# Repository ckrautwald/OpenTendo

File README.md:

<br />

# Open 'Tendo

This fork develops modern component substitutions. The motherboard now replaces
RA2 with four 0805 resistors (R20–R23). See [RA2 modernization](RA2-MODERNIZATION.md)
for the change, validation results, and prototype limitations. Open the board in
KiCad 10.
An Open-Source HardWare (OSHW) recreation of the original 1985 Front-Loading NES motherboard.

## Note on RGB and HDMI

Neither RGB nor HDMI video output were or are a goal of the OpenTendo project, the goal was/is documentation and preservation, and the project was an exercise in reverse engineering. As such "improved" video outputs will not be added to OpenTendo.

NESRGB and Hi-Def NES can be installed as normal, but will not be incorporated into the OpenTendo PCB

## Repository Structure
### Branches
| Branch | Description |
| ------ | ----------- |
| master | Latest revision of OpenTendo. This is a almost 1:1 of the OEM NES. |
| modded | Modded version of the latest revision (`master`). This houses any modification that is not in the OEM NES. |
| vX.X | Previous revisions of OpenTendo. (*ex.* v1.3) |
| vX.X_modded | Modded version of a previous revision. (*ex.* v1.3_modded) |

### File Structure
```
.
├── BOM              # Contains the bill of materials.
├── Board Files      # Contains all files necessary to open the project in KiCad.
|   └── Libraries    # Contains a library of all of the custom footprints used on the board.
├── Scans            # Contains the scans of the OEM NES board.
└── Schematics       # Contains schematics for the OEM frontloading NES board revisions,
                       some schematics represent more than one revision
```

The gerber files required to order PCBs can be found under [releases](https://github.com/Redherring32/OpenTendo/releases).

## Recommended PCB specs
* 2 layers

* 119mmx196mm

* 1.6mm thickness

* HASL or ENiG surface finish

* And any color you want!

> [!IMPORTANT]
> OpenTendo have some solder mask overlapping the edge connector to secure the pads and the thin traces. Some fabricators might see this as an error and might try to fix it.
>
> We recommend leaving a note saying that the solder mask overlap on the edge connector is intentional and NOT an error when ordering the PCB.

The design is as true to the original board as possible, with subtle changes where needed to compensate for outdated/unsourcable parts,
as well as some improvements. (Expansion audio enabled, and other minor changes)

Since this project is open-source you may do as you like with it, whether that is to make boards for personal use, sell replacement NES boards, or to use the provided info for further custom PCB work/designs.

I am not in any way affiliated with Nintendo, I'm just doing this in my free time as a stepping stone into further Reverse Engineering work.

>[!NOTE]
> Please check the [BOM](./BOM#from-the-oem-nes) for the list of components needed from the OEM NES

## License

Licensed under
the TAPR Open Hardware License (www.tapr.org/OHL)

©Redherring32 2019-2024

## Credits
*=Lockster=* - Helping me tremendously along the way, keeping me from going insane, and cleaning up/helping with the final schematic. 

*Krzysiobal* - Putting together the NES-CPU-11 schematic that my schematic is largely referrenced against.

*[Muramasa](https://www.muramasaentertainment.com/)* - Ported to KiCad v8, PCB clean up, and fixing the EXP port footprint.

*[Kamoteshake](https://github.com/kamoteshake)* - Schematic clean up and fixing the EXP port footprint.

And to all of the awesome people in the NES scene, I wouldn't have been able to do this without the awesome work that some very clever people did before I got here.

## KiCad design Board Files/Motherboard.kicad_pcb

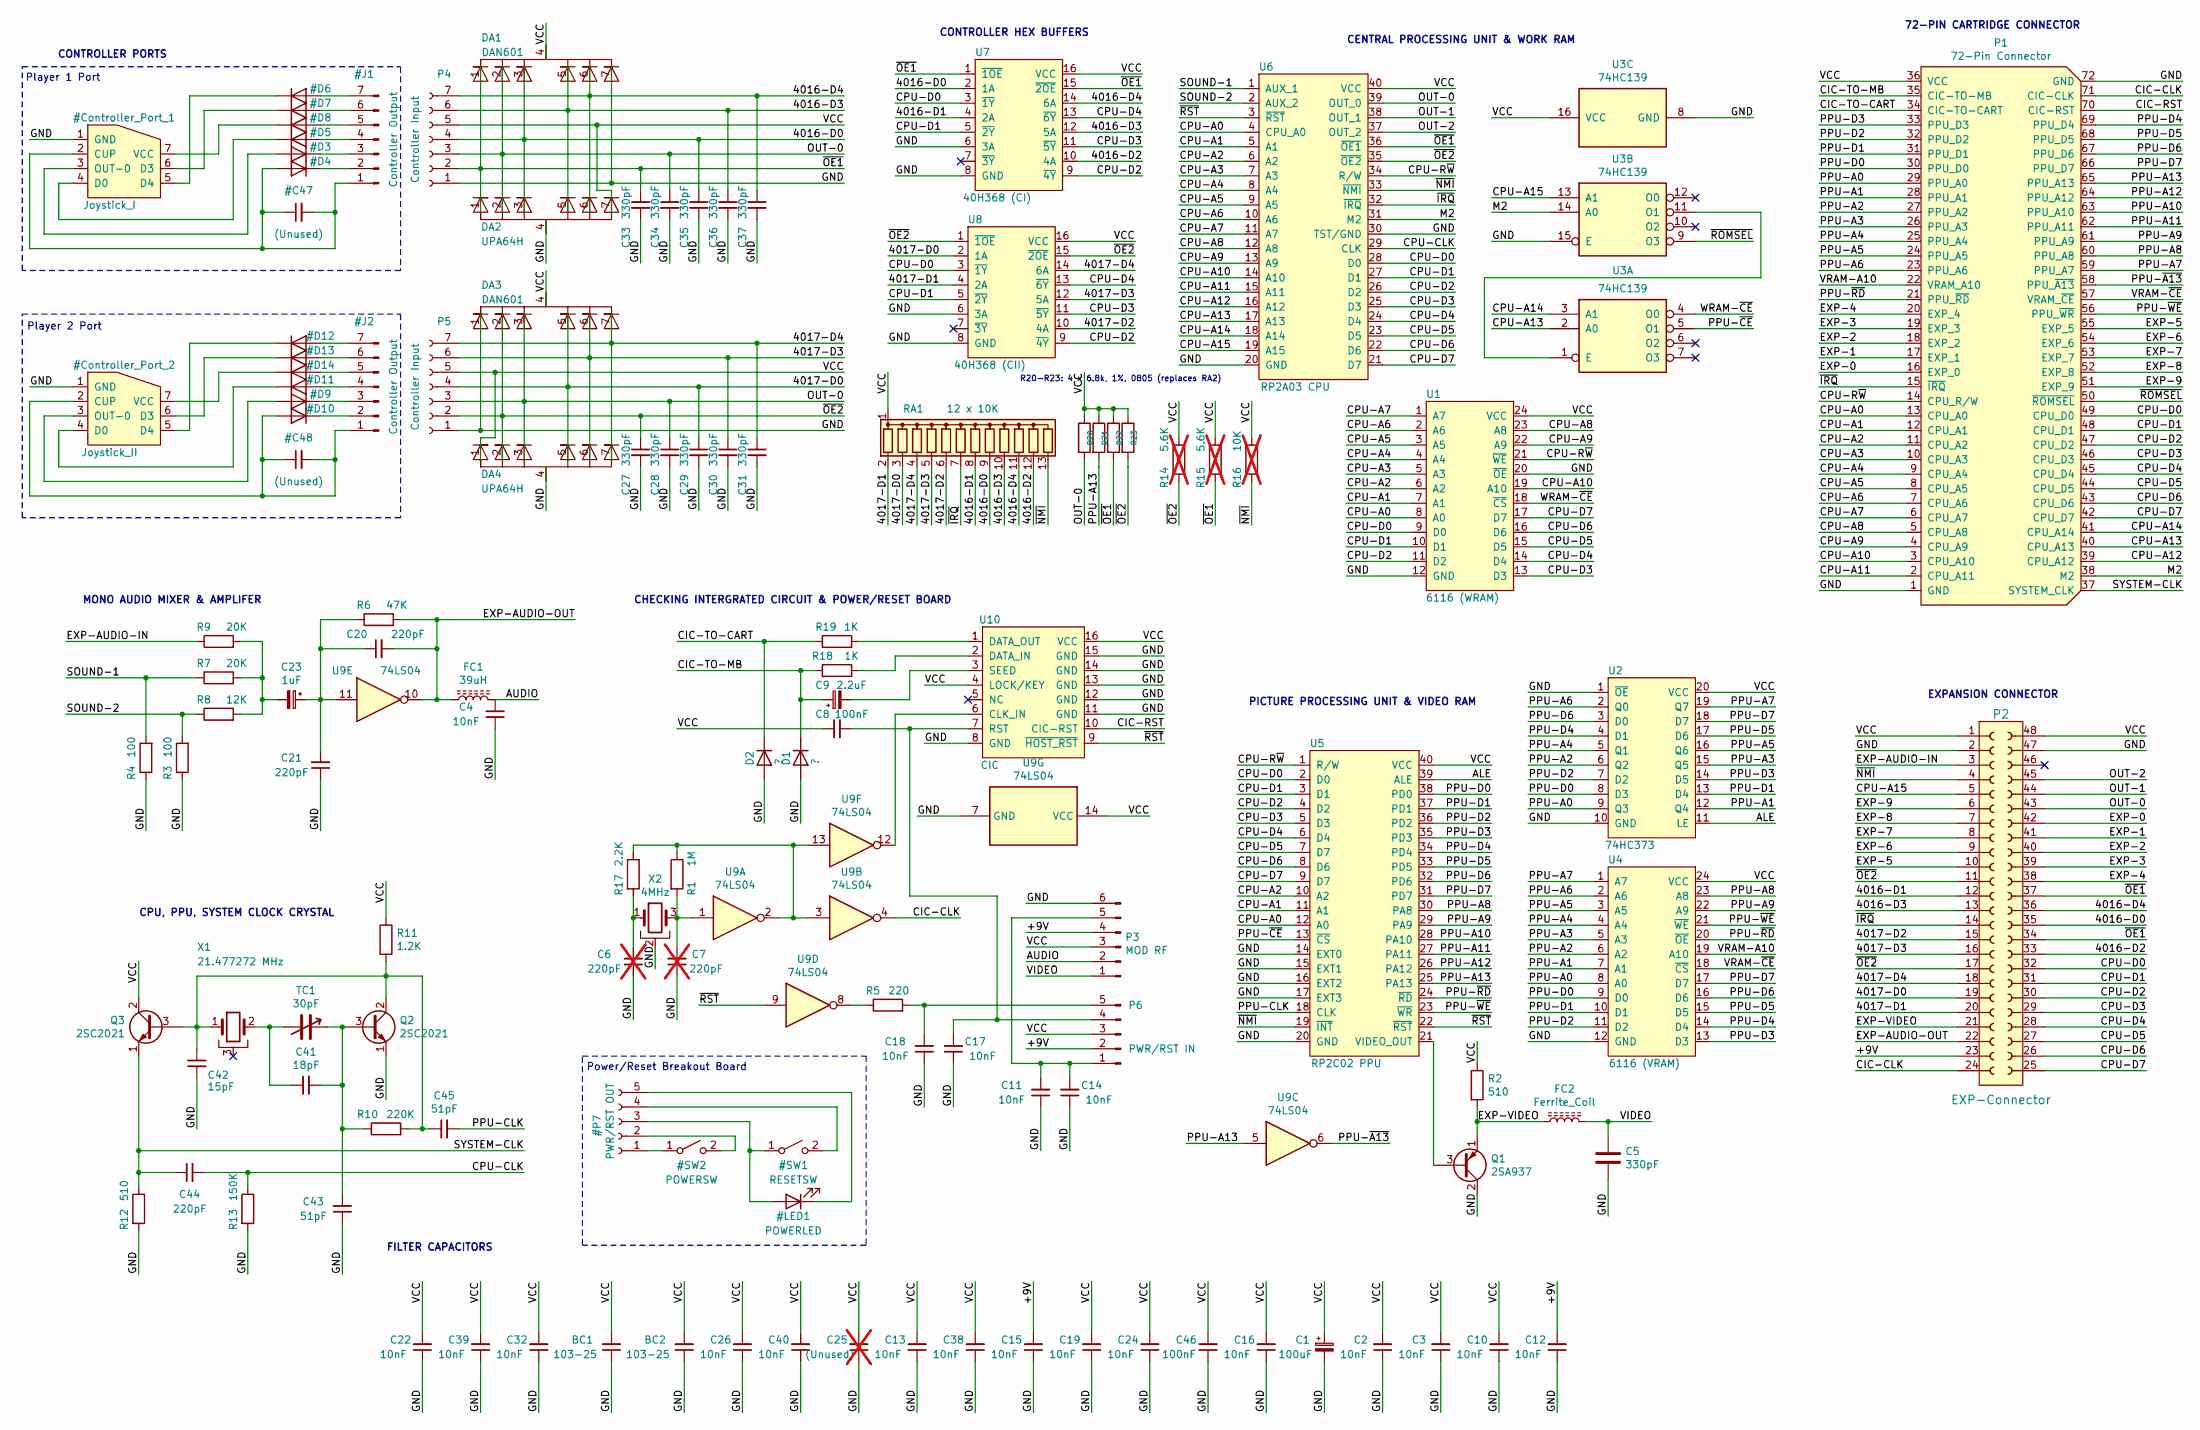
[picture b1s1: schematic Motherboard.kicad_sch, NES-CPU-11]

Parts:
BC1, BC2: 103-25; C_Disc_D6.0mm_W2.5mm_P5.00mm
C1: 100uF; CP_Radial_D5.0mm_P2.50mm
C2, C3, C4, C10, C11, C12, C13, C14, C15, C16, C17, C18, C19, C22, C24, C26, C32, C38, C39, C40: 10nF; C_Disc_D5.0mm_W2.5mm_P5.00mm
C5: 330pF; C_Disc_D3.0mm_W2.0mm_P2.50mm
C6, C7: 220pF; C_Disc_D3.0mm_W1.6mm_P2.50mm; not fitted
C8, C46: 100nF; C_Disc_D7.0mm_W2.5mm_P5.00mm
C9: 2.2uF; CP_Radial_D5.0mm_P2.50mm
C20, C21, C44: 220pF; C_Disc_D3.0mm_W1.6mm_P2.50mm
C23: 1uF; CP_Radial_D5.0mm_P2.50mm
C25: (Unused); C_Disc_D5.0mm_W2.5mm_P5.00mm; not fitted
C27, C28, C29, C30, C31, C33, C34, C35, C36, C37: 330pF; C_Disc_D3.0mm_W1.6mm_P2.50mm
C41: 18pF; C_Disc_D3.0mm_W2.0mm_P2.50mm
C42: 15pF; C_Disc_D3.4mm_W2.1mm_P2.50mm
C43, C45: 51pF; C_Disc_D3.4mm_W2.1mm_P2.50mm
D1, D2: ?; D_DO-35_SOD27_P10.16mm_Horizontal
DA1, DA3: DAN601; R_Array_SIP7
DA2, DA4: UPA64H; R_Array_SIP7
FC1: 39uH; R_Axial_DIN0207_L6.3mm_D2.5mm_P10.16mm_Horizontal
FC2: Ferrite_Coil; R_Axial_DIN0207_L6.3mm_D2.5mm_P10.16mm_Horizontal
P1: 72-Pin Connector; NES_Edge_Connector
P2: EXP-Connector; EXP_Header
P3: MOD RF; Mod_RF
P4, P5: Controller Input; JST_PH_S7B-PH-K_1x07_P2.00mm_Horizontal
P6: PWR/RST IN; PowerReset-switch-In
Q1: 2SA937; TO-126-3_Vertical_Short
Q2, Q3: 2SC2021; TO-126-3_Vertical_Short
R1: 1M; R_Axial_DIN0207_L6.3mm_D2.5mm_P10.16mm_Horizontal
R2, R12: 510; R_Axial_DIN0207_L6.3mm_D2.5mm_P10.16mm_Horizontal
R3, R4: 100; R_Axial_DIN0207_L6.3mm_D2.5mm_P10.16mm_Horizontal
R5: 220; R_Axial_DIN0207_L6.3mm_D2.5mm_P10.16mm_Horizontal
R6: 47K; R_Axial_DIN0207_L6.3mm_D2.5mm_P10.16mm_Horizontal
R7, R9: 20K; R_Axial_DIN0207_L6.3mm_D2.5mm_P10.16mm_Horizontal
R8: 12K; R_Axial_DIN0207_L6.3mm_D2.5mm_P10.16mm_Horizontal
R10: 220K; R_Axial_DIN0207_L6.3mm_D2.5mm_P10.16mm_Horizontal
R11: 1.2K; R_Axial_DIN0207_L6.3mm_D2.5mm_P10.16mm_Horizontal
R13: 150K; R_Axial_DIN0207_L6.3mm_D2.5mm_P10.16mm_Horizontal
R14, R15: 5.6K; R_Axial_DIN0207_L6.3mm_D2.5mm_P10.16mm_Horizontal; not fitted
R16: 10K; R_Axial_DIN0207_L6.3mm_D2.5mm_P10.16mm_Horizontal; not fitted
R17: 2.2K; R_Axial_DIN0207_L6.3mm_D2.5mm_P10.16mm_Horizontal
R18, R19: 1K; R_Axial_DIN0207_L6.3mm_D2.5mm_P10.16mm_Horizontal
R20, R21, R22, R23: 6.8k; R_0805_2012Metric_Pad1.20x1.40mm_HandSolder; MPN RC0805FR-076K8L
RA1: 12 x 10K; R_Array_SIP13
TC1: 30pF; TrimmerCap-THT
U1: 6116 (WRAM); DIP-24_W15.24-7.62mm
U2: 74HC373; DIP-20_W7.62mm
U3: 74HC139; DIP-16_W7.62mm
U4: 6116 (VRAM); DIP-24_W15.24-7.62mm
U5: RP2C02 PPU; DIP-40_W15.24mm
U6: RP2A03 CPU; DIP-40_W15.24mm
U7: 40H368 (CI); DIP-16_W7.62mm
U8: 40H368 (CII); DIP-16_W7.62mm
U9: 74LS04; DIP-14_W7.62mm
U10: CIC; DIP-16_W7.62mm
X1: 21.477272 MHz; Crystal_HC49-U_Horizontal_1EP_style2
X2: 4MHz; Resonator_Murata_CSTLSxxxG-3Pin_W8.0mm_H3.0mm

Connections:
/4016-D0: C35.1, DA1.3, DA2.3, P2.35, P4.4, RA1.9 (R8), U7.2 (1A)
/4016-D1: P2.12, RA1.8 (R7), U7.4 (2A)
/4016-D2: P2.33, RA1.12 (R11), U7.10 (4A)
/4016-D3: C36.1, DA1.5, DA2.5, P2.13, P4.6, RA1.10 (R9), U7.12 (5A)
/4016-D4: C37.1, DA1.6, DA2.6, P2.36, P4.7, RA1.11 (R10), U7.14 (6A)
/4017-D0: C29.1, DA3.5, DA4.5, P2.19, P5.4, RA1.3 (R2), U8.2 (1A)
/4017-D1: P2.20, RA1.2 (R1), U8.4 (2A)
/4017-D2: P2.15, RA1.6 (R5), U8.10 (4A)
/4017-D3: C30.1, DA3.6, DA4.6, P2.16, P5.6, RA1.5 (R4), U8.12 (5A)
/4017-D4: C31.1, DA3.7, DA4.7, P2.18, P5.7, RA1.4 (R3), U8.14 (6A)
/+9V: C12.2, C15.2, P2.23, P3.4, P6.2
/ALE: U2.11 (LE), U5.39 (ALE)
/AUDIO: C4.2, FC1.2, P3.2
/CIC-CLK: P1.71 (CIC-CLK), P2.24, U9.4
/CIC-RST: P1.70 (CIC-RST), U10.10 (CIC-RST)
/CIC-TO-CART: D2.1 (K), P1.34 (CIC-TO-CART), R19.1
/CIC-TO-MB: C9.1, D1.1 (K), P1.35 (CIC-TO-MB), R18.1
/CPU-A0: P1.13 (CPU_A0), U1.8 (A0), U5.12 (A0), U6.4 (CPU_A0)
/CPU-A1: P1.12 (CPU_A1), U1.7 (A1), U5.11 (A1), U6.5 (A1)
/CPU-A2: P1.11 (CPU_A2), U1.6 (A2), U5.10 (A2), U6.6 (A2)
/CPU-A3: P1.10 (CPU_A3), U1.5 (A3~), U6.7 (A3)
/CPU-A4: P1.9 (CPU_A4), U1.4 (A4~), U6.8 (A4)
/CPU-A5: P1.8 (CPU_A5), U1.3 (A5~), U6.9 (A5)
/CPU-A6: P1.7 (CPU_A6), U1.2 (A6~), U6.10 (A6)
/CPU-A7: P1.6 (CPU_A7), U1.1 (A7), U6.11 (A7)
/CPU-A8: P1.5 (CPU_A8), U1.23 (A8), U6.12 (A8)
/CPU-A9: P1.4 (CPU_A9), U1.22 (A9), U6.13 (A9)
/CPU-A10: P1.3 (CPU_A10), U1.19 (A10), U6.14 (A10)
/CPU-A11: P1.2 (CPU_A11), U6.15 (A11)
/CPU-A12: P1.39 (CPU_A12), U6.16 (A12)
/CPU-A13: P1.40 (CPU_A13), U3.2 (A0), U6.17 (A13)
/CPU-A14: P1.41 (CPU_A14), U3.3 (A1), U6.18 (A14)
/CPU-A15: P2.5, U3.13 (A1), U6.19 (A15)
/CPU-CLK: C44.2, R13.1, U6.29 (CLK)
/CPU-D0: P1.49 (CPU_D0), P2.32, U1.9 (D0), U5.2 (D0), U6.28 (D0), U7.3 (~1Y), U8.3 (~1Y)
/CPU-D1: P1.48 (CPU_D1), P2.31, U1.10 (D1), U5.3 (D1), U6.27 (D1), U7.5 (~2Y), U8.5 (~2Y)
/CPU-D2: P1.47 (CPU_D2), P2.30, U1.11 (D2), U5.4 (D2), U6.26 (D2), U7.9 (~4Y), U8.9 (~4Y)
/CPU-D3: P1.46 (CPU_D3), P2.29, U1.13 (D3), U5.5 (D3), U6.25 (D3), U7.11 (~5Y), U8.11 (~5Y)
/CPU-D4: P1.45 (CPU_D4), P2.28, U1.14 (D4), U5.6 (D4), U6.24 (D4), U7.13 (~6Y), U8.13 (~6Y)
/CPU-D5: P1.44 (CPU_D5), P2.27, U1.15 (D5), U5.7 (D7), U6.23 (D5)
/CPU-D6: P1.43 (CPU_D6), P2.26, U1.16 (D6), U5.8 (D6), U6.22 (D6)
/CPU-D7: P1.42 (CPU_D7), P2.25, U1.17 (D7), U5.9 (D7), U6.21 (D7)
/CPU-R~W: P1.14 (CPU_R/W), U1.21 (~WE), U5.1 (R/W), U6.34 (R/W)
/EXP-0: P1.16 (EXP_0), P2.42
/EXP-1: P1.17 (EXP_1), P2.41
/EXP-2: P1.18 (EXP_2), P2.40
/EXP-3: P1.19 (EXP_3), P2.39
/EXP-4: P1.20 (EXP_4), P2.38
/EXP-5: P1.55 (EXP_5), P2.10
/EXP-6: P1.54 (EXP_6), P2.9
/EXP-7: P1.53 (EXP_7), P2.8
/EXP-8: P1.52 (EXP_8), P2.7
/EXP-9: P1.51 (EXP_9), P2.6
/EXP-AUDIO-IN: P2.3, R9.1
/EXP-AUDIO-OUT: C20.2, FC1.1, P2.22, R6.2, U9.10
/EXP-VIDEO: FC2.1, P2.21, Q1.1 (E), R2.2
/GND: BC1.1, BC2.1, C1.2, C2.1, C3.1, C4.1, C5.2, C6.1, C7.1, C10.1, C11.1, C12.1, C13.1, C14.1, C15.1, C16.1, C17.1, C18.1, C19.1, C21.1, C22.1, C24.1, C25.1, C26.1, C27.2, C28.2, C29.2, C30.2, C31.2, C32.1, C33.2, C34.2, C35.2, C36.2, C37.2, C38.1, C39.1, C40.1, C42.1, C43.1, C46.1, D1.2 (A), D2.2 (A), DA1.7, DA2.4, DA3.1, DA4.4, P1.1 (GND), P1.72 (GND), P2.2, P2.47, P3.6, P4.1, P5.1, Q1.2 (C), Q2.1 (E), R3.1, R4.1, R12.2, R13.2, U1.12 (GND~), U1.20 (~OE), U2.1 (~OE), U2.10 (GND), U3.8 (GND), U3.15 (E), U4.12 (GND~), U5.14 (EXT0), U5.15 (EXT1), U5.16 (EXT2), U5.17 (EXT3), U5.20 (GND), U6.20 (GND), U6.30 (TST/GND), U7.6 (3A), U7.8 (GND), U8.6 (3A), U8.8 (GND), U9.7 (GND), U10.8 (GND), U10.11 (GND), U10.12 (GND), U10.13 (GND), U10.14 (GND), U10.15 (GND), X2.2
/M2: P1.38 (M2), U3.14 (A0), U6.31 (M2)
/OUT-0: C28.1, C34.1, DA1.2, DA2.2, DA3.3, DA4.3, P2.43, P4.3, P5.3, R20.2, U6.39 (OUT_0)
/OUT-1: P2.44, U6.38 (OUT_1)
/OUT-2: P2.45, U6.37 (OUT_2)
/PPU-A0: P1.29 (PPU_A0), U2.9 (Q3), U4.8 (A0)
/PPU-A1: P1.28 (PPU_A1), U2.12 (Q4), U4.7 (A1)
/PPU-A2: P1.27 (PPU_A2), U2.6 (Q2), U4.6 (A2)
/PPU-A3: P1.26 (PPU_A3), U2.15 (Q5), U4.5 (A3~)
/PPU-A4: P1.25 (PPU_A4), U2.5 (Q1), U4.4 (A4~)
/PPU-A5: P1.24 (PPU_A5), U2.16 (Q6), U4.3 (A5~)
/PPU-A6: P1.23 (PPU_A6), U2.2 (Q0), U4.2 (A6~)
/PPU-A7: P1.59 (PPU_A7), U2.19 (Q7), U4.1 (A7)
/PPU-A8: P1.60 (PPU_A8), U4.23 (A8), U5.30 (PA8)
/PPU-A9: P1.61 (PPU_A9), U4.22 (A9), U5.29 (PA9)
/PPU-A10: P1.63 (PPU_A10), U5.28 (PA10)
/PPU-A11: P1.62 (PPU_A11), U5.27 (PA11)
/PPU-A12: P1.64 (PPU_A12), U5.26 (PA12)
/PPU-A13: P1.65 (PPU_A13), R21.2, U5.25 (PA13), U9.5
/PPU-CLK: C45.2, U5.18 (CLK)
/PPU-D0: P1.30 (PPU_D0), U2.8 (D3), U4.9 (D0), U5.38 (PD0)
/PPU-D1: P1.31 (PPU_D1), U2.13 (D4), U4.10 (D1), U5.37 (PD1)
/PPU-D2: P1.32 (PPU_D2), U2.7 (D2), U4.11 (D2), U5.36 (PD2)
/PPU-D3: P1.33 (PPU_D3), U2.14 (D5), U4.13 (D3), U5.35 (PD3)
/PPU-D4: P1.69 (PPU_D4), U2.4 (D1), U4.14 (D4), U5.34 (PD4)
/PPU-D5: P1.68 (PPU_D5), U2.17 (D6), U4.15 (D5), U5.33 (PD5)
/PPU-D6: P1.67 (PPU_D6), U2.3 (D0), U4.16 (D6), U5.32 (PD6)
/PPU-D7: P1.66 (PPU_D7), U2.18 (D7), U4.17 (D7), U5.31 (PD7)
/PPU-~A13: P1.58 (PPU_~A13), U9.6
/PPU-~CE: U3.5 (O1), U5.13 (~CS)
/PPU-~RD: P1.21 (PPU_~RD), U4.20 (~OE), U5.24 (~RD)
/PPU-~WE: P1.56 (PPU_~WR), U4.21 (~WE), U5.23 (~WR)
/SOUND-1: R4.2, R7.1, U6.1 (AUX_1)
/SOUND-2: R3.2, R8.1, U6.2 (AUX_2)
/SYSTEM-CLK: C44.1, P1.37 (SYSTEM_CLK), Q3.1 (E), R12.1
/VCC: BC1.2, BC2.2, C1.1, C2.2, C3.2, C8.1, C10.2, C13.2, C16.2, C19.2, C22.2, C24.2, C25.2, C26.2, C32.2, C38.2, C39.2, C40.2, C46.2, DA1.4, DA2.7, DA3.4, DA4.1, P1.36 (VCC), P2.1, P2.48, P3.3, P4.5, P5.5, P6.3, Q3.2 (C), R2.1, R11.1, R14.1, R15.1, R16.1, R20.1, R21.1, R22.1, R23.1, RA1.1 (common), U1.24 (VCC), U2.20 (VCC), U3.16 (VCC), U4.24 (VCC), U5.40 (VCC), U6.40 (VCC), U7.16 (VCC), U8.16 (VCC), U9.14 (VCC), U10.4 (LOCK/KEY), U10.16 (VCC)
/VIDEO: C5.1, FC2.2, P3.1
/VRAM-A10: P1.22 (VRAM_A10), U4.19 (A10)
/VRAM-~CE: P1.57 (VRAM_~CE), U4.18 (~CS)
/WRAM-~CE: U1.18 (~CS), U3.4 (O0)
/~IRQ: P1.15 (~IRQ), P2.14, RA1.7 (R6), U6.32 (~IRQ)
/~NMI: P2.4, R16.2, RA1.13 (R12), U5.19 (~INT), U6.33 (~NMI)
/~OE1: C33.1, DA1.1, DA2.1, P2.34, P2.37, P4.2, R15.2, R22.2, U6.36 (~OE1), U7.1 (~1OE), U7.15 (~2OE)
/~OE2: C27.1, DA3.2, DA4.2, P2.11, P2.17, P5.2, R14.2, R23.2, U6.35 (~OE2), U8.1 (~1OE), U8.15 (~2OE)
/~ROMSEL: P1.50 (~ROMSEL), U3.9 (O3)
/~RST: U5.22 (~RST), U6.3 (~RST), U9.9, U10.9 (~HOST_RST)
unnamed: C6.2, R17.2, X2.1
unnamed: C7.2, R1.2, U9.1, X2.3
unnamed: C20.1, C21.2, C23.1, R6.1, U9.11
unnamed: C23.2, R7.2, R8.2, R9.2
unnamed: C41.1, TC1.2, X1.2
unnamed: C11.2, C14.2, P3.5, P6.1
unnamed: C8.2, C17.2, P6.4, U10.7 (RST)
unnamed: C18.2, P6.5, R5.2
unnamed: Q1.3 (B), U5.21 (VIDEO_OUT)
unnamed: C41.2, C43.2, Q2.3 (B), R10.1, TC1.1
unnamed: C42.2, C45.1, Q2.2 (C), Q3.3 (B), R10.2, R11.2, X1.1
unnamed: R1.1, R17.1, U9.2, U9.3, U9.13
unnamed: R5.1, U9.8
unnamed: U3.1 (E), U3.11 (O1)
unnamed: U9.12, U10.6 (CLK_IN)
unnamed: R18.2, U10.2 (DATA_IN)
unnamed: R19.2, U10.1 (DATA_OUT)
unnamed: C9.2, U10.3 (SEED)

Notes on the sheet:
72-PIN CARTRIDGE CONNECTOR
MONO AUDIO MIXER & AMPLIFER
CENTRAL PROCESSING UNIT & WORK RAM
CONTROLLER PORTS
EXPANSION CONNECTOR
FILTER CAPACITORS
Player 2 Port
Player 1 Port
Power/Reset Breakout Board
CHECKING INTERGRATED CIRCUIT & POWER/RESET BOARD
PICTURE PROCESSING UNIT & VIDEO RAM
CPU, PPU, SYSTEM CLOCK CRYSTAL
CONTROLLER HEX BUFFERS
R20-R23: 4 x 6.8k, 1%, 0805 (replaces RA2)

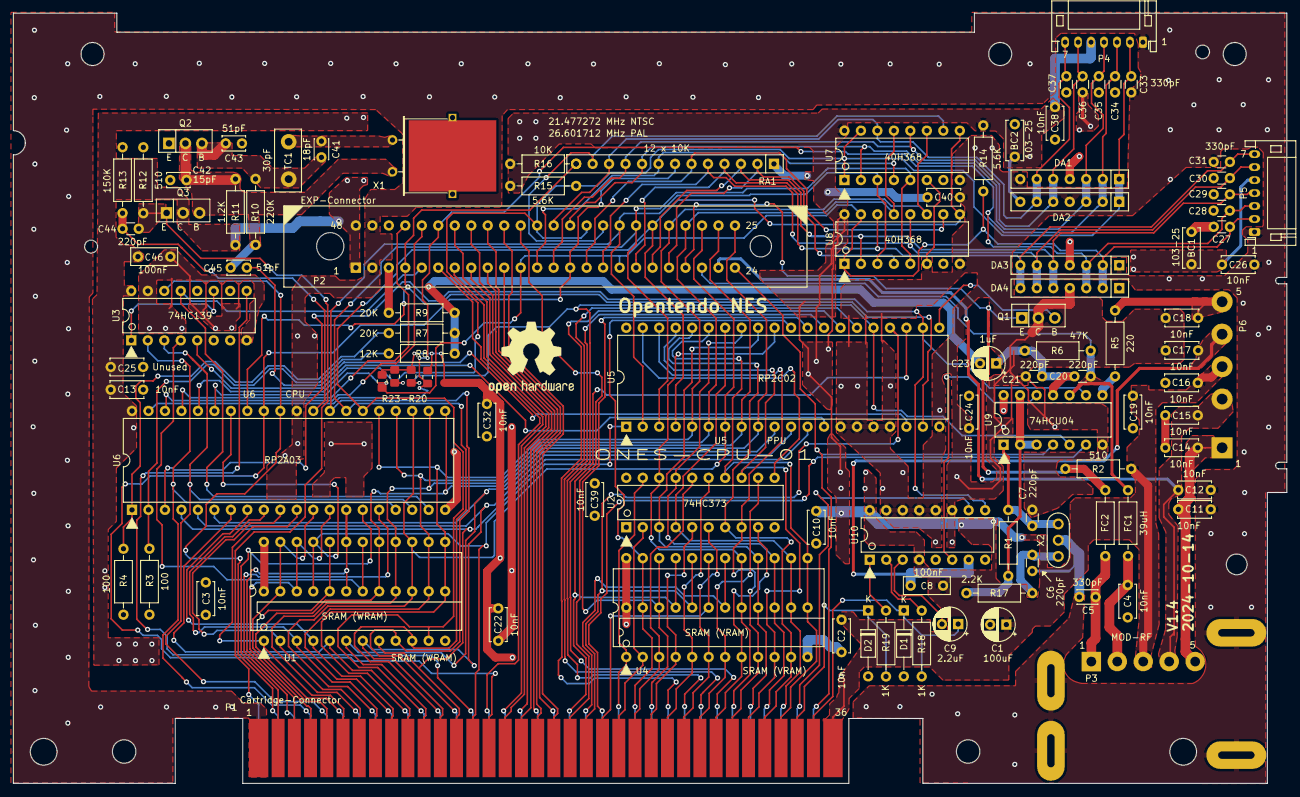
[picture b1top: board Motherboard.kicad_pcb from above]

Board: 2 copper layers, 196.3 x 118.7 mm, 102 parts (0 on the bottom side), 120 nets.

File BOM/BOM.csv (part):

Query,Qty,Manufacturer,MPN,Octopart URL,Part Description,Description,Schematic Reference,Internal Part Number,Lifecycle,Lead Time,RoHS,Total Qty (@ Batch Size: 1),SKU,SKU,SKU,SKU,SKU,Packaging,Packaging,Packaging,Packaging,Packaging,Unit Price (@ Batch Size: 1),Unit Price (@ Batch Size: 1),Unit Price (@ Batch Size: 1),Unit Price (@ Batch Size: 1),Unit Price (@ Batch Size: 1),In Stock,In Stock,In Stock,In Stock,In Stock,MOQ,MOQ,MOQ,MOQ,MOQ,URL,URL,URL,URL,URL,Distributor [Lowest Price (Preferred Distributors)],SKU [Lowest Price (Preferred Distributors)],Packaging [Lowest Price (Preferred Distributors)],Unit Price (@ Batch Size: 1) [Lowest Price (Preferred Distributors)],Line Total [Lowest Price (Preferred Distributors)],Batch Total [Lowest Price (Preferred Distributors)],In Stock [Lowest Price (Preferred Distributors)],MOQ [Lowest Price (Preferred Distributors)],URL [Lowest Price (Preferred Distributors)],Notes
,,,,,,,,,,,,,Digi-Key,Mouser,Newark,Onlinecomponents.com,RS Components,Digi-Key,Mouser,Newark,Onlinecomponents.com,RS Components,Digi-Key,Mouser,Newark,Onlinecomponents.com,RS Components,Digi-Key,Mouser,Newark,Onlinecomponents.com,RS Components,Digi-Key,Mouser,Newark,Onlinecomponents.com,RS Components,Digi-Key,Mouser,Newark,Onlinecomponents.com,RS Components,,,,,,,,,,
CSTLS4M00G56-B0,1,Murata,CSTLS4M00G56-B0,https://octopart.com/cstls4m00g56-b0-murata-10326657,Ceramic Resonator 4MHz ±0.5% (Tol) -0.4/0.2% (Stability) 47pF 30Ohm 3-Pin Thru-Hole Bulk,,X2,,NRND (Last Updated: 2 weeks ago),15w,Compliant,1,490-7036-ND,81-CSTLS4M00G56-B0,70AC3726,,,Bulk,Bulk,,,,0.21,0.21,0.209,,,4715,2001,324,,,1,1,1,,,https://octopart.com/opatz8j6/a1?t=cfxySeqOX8aMYG3G4lECwjEoY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,https://octopart.com/opatz8j6/a1?t=V3R7cpLq0kgXtluYTNERcbOHe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,https://octopart.com/opatz8j6/a1?t=XYToUbM6IMgRZrj4g3DdaitNe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,,,Newark,70AC3726,,0.209,0.209,0.209,324,1,https://octopart.com/opatz8j6/a1?t=XYToUbM6IMgRZrj4g3DdaitNe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,
ECS-214-S-4X,1,ECS International,ECS-214-S-4X,https://octopart.com/ecs-214-s-4x-ecs+international-88334749,,,X1,,,,Compliant,1,,520-HCU2147-SX,,,,,Bulk,,,,,0.69,,,,,558,,,,,1,,,,,https://octopart.com/opatz8j6/a1?t=KB6qdfYPWqJU6lg3CsOjnDbhv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,,,,Mouser,520-HCU2147-SX,Bulk,0.69,0.69,0.69,558,1,https://octopart.com/opatz8j6/a1?t=KB6qdfYPWqJU6lg3CsOjnDbhv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,
SN74HCU04N,1,Texas Instruments,SN74HCU04N,https://octopart.com/sn74hcu04n-texas+instruments-465549,Gate / Inverter Logic IC Leaded Process; function (IC): Hex Inverter; Base Number: 7404,,U9,,Production (Last Updated: 1 week ago),1w,Compliant,1,296-9820-5-ND,595-SN74HCU04N,,,,Tube,Tube,,,,0.63,0.59,,,,2448,1088,,,,1,1,,,,https://octopart.com/opatz8j6/a1?t=TbsfS7VVlIRgcE-yO74488-vg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,https://octopart.com/opatz8j6/a1?t=rr1pfHe_NOq3UB9G2hPgq_Pq5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,,,,Mouser,595-SN74HCU04N,Tube,0.59,0.59,0.59,1088,1,https://octopart.com/opatz8j6/a1?t=rr1pfHe_NOq3UB9G2hPgq_Pq5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,
SN74HC368N,1,Texas Instruments,SN74HC368N,https://octopart.com/sn74hc368n-texas+instruments-51845,Buffer/Line Driver 6-CH Inverting 3-ST CMOS 16-Pin PDIP Tube,,U8,,Production (Last Updated: 1 week ago),1w,Compliant,1,296-8308-5-ND,595-SN74HC368N,,,,Tube,Tube,,,,0.65,0.57,,,,4259,951,,,,1,1,,,,https://octopart.com/opatz8j6/a1?t=xXsxuLQlsp8rvDh0OFIPojX6s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,https://octopart.com/opatz8j6/a1?t=-K2ELcLJ8J42ZGu3GTQUl3Wlw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,,,,Mouser,595-SN74HC368N,Tube,0.57,0.57,0.57,951,1,https://octopart.com/opatz8j6/a1?t=-K2ELcLJ8J42ZGu3GTQUl3Wlw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,
SN74HC368N,1,Texas Instruments,SN74HC368N,https://octopart.com/sn74hc368n-texas+instruments-51845,Buffer/Line Driver 6-CH Inverting 3-ST CMOS 16-Pin PDIP Tube,,U7,,Production (Last Updated: 1 week ago),1w,Compliant,1,296-8308-5-ND,595-SN74HC368N,,,,Tube,Tube,,,,0.65,0.57,,,,4259,951,,,,1,1,,,,https://octopart.com/opatz8j6/a1?t=xXsxuLQlsp8rvDh0OFIPojX6s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,https://octopart.com/opatz8j6/a1?t=-K2ELcLJ8J42ZGu3GTQUl3Wlw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,,,,Mouser,595-SN74HC368N,Tube,0.57,0.57,0.57,951,1,https://octopart.com/opatz8j6/a1?t=-K2ELcLJ8J42ZGu3GTQUl3Wlw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,
ED40DT,2,On Shore Technology,ED40DT,https://octopart.com/ed40dt-on+shore+technology-5349672,Conn DIP Socket SKT 40 POS Solder ST Thru-Hole,,"U5, U6",,,8w,Compliant,2,ED3048-5-ND,,,,,Tube,,,,,0.59,,,,,1677,,,,,1,,,,,https://octopart.com/opatz8j6/a1?t=QC8N5x93kpnCsLozEZarLQw-0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,,,,,DigiKey,ED3048-5-ND,Tube,0.59,1.18,1.18,1677,1,https://octopart.com/opatz8j6/a1?t=QC8N5x93kpnCsLozEZarLQw-0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,
SN74HC139N,1,Texas Instruments,SN74HC139N,https://octopart.com/sn74hc139n-texas+instruments-17212,Decoder/Demultiplexer; Dual 2 to 4 Line Decoder-Demultiplexer; 0 to 5 V; PDIP,,U3,,Production (Last Updated: 1 week ago),1w,Compliant,1,296-8230-5-ND,595-SN74HC139N,33AH4851,,,Tube,Tube,,,,1.31,1.28,0.147,,,102,1545,19,,,1,1,1,,,https://octopart.com/opatz8j6/a1?t=BsouU8LiPA5MYxD0V_ZUYWajK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,https://octopart.com/opatz8j6/a1?t=pxnyt0Fjp22FP7gwxST42hPp6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,https://octopart.com/opatz8j6/a1?t=wUglIata6E3bLIa_p_fNf-xcc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,,,Newark,33AH4851,,0.147,0.147,0.147,19,1,https://octopart.com/opatz8j6/a1?t=wUglIata6E3bLIa_p_fNf-xcc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,
SN74HC373N,1,Texas Instruments,SN74HC373N,https://octopart.com/sn74hc373n-texas+instruments-471147,Latch; Octal Transparent D-Type Latch; 0 to 5 V; 500 ns (Max.) @ 4.5 V; PDIP-N,,U2,,Production (Last Updated: 1 week ago),6w,Compliant,1,296-1591-5-ND,595-SN74HC373N,29AH1488,,,Tube,Tube,,,,0.82,0.78,0.822,,,0,130,50,,,1,1,1,,,https://octopart.com/opatz8j6/a1?t=_5FZWgO-aXc4crPGRvFDKKbAK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,https://octopart.com/opatz8j6/a1?t=CcEa3PiL64gLYv9PEXPKYATCD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,https://octopart.com/opatz8j6/a1?t=ggLojo4GALDrhtcxJ5oQY4DM7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,,,Mouser,595-SN74HC373N,Tube,0.78,0.78,0.78,130,1,https://octopart.com/opatz8j6/a1?t=CcEa3PiL64gLYv9PEXPKYATCD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,
6116SA15SOG,2,Renesas,6116SA15SOG,https://octopart.com/6116sa15sog-renesas-106910578,SRAM Chip Async Single 5V 16K-Bit 2K x 8 15ns 24-Pin SOIC Tube/Tray,,"U1, U4",,Production (Last Updated: 1 week ago),1w,Compliant,2,6116SA15SOG-ND,972-6116SA15SOG,,,,Tube,Tube,,,,6.44,6.19,,,,282,202,,,,1,1,,,,https://octopart.com/opatz8j6/a1?t=blbDHIIVNzWF6pg-c9yHvwcBj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,https://octopart.com/opatz8j6/a1?t=I2qiyp1hRZ-fiOufk1QEFq6DN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,,,,Mouser,972-6116SA15SOG,Tube,6.19,12.38,12.38,202,1,https://octopart.com/opatz8j6/a1?t=I2qiyp1hRZ-fiOufk1QEFq6DN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,Alternate: Renesas 6116SA15TPG
PA0009,2,Chip Quik,PA0009,https://octopart.com/pa0009-chip+quik-51024752,SOIC-24 to DIP-24 SMT Adapter,,"U1, U4",,,4w,Compliant,2,PA0009-ND,910-PA0009,,,,Bulk,,,,,5.29,5.29,,,,222,100,,,,1,1,,,,https://octopart.com/opatz8j6/a1?t=KaDTUL_lAGDmjjspp00bL0S0e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,https://octopart.com/opatz8j6/a1?t=bCU1OnnXYY135DnrfQUFJ3Px6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,,,,DigiKey,PA0009-ND,Bulk,5.29,10.58,10.58,222,1,https://octopart.com/opatz8j6/a1?t=KaDTUL_lAGDmjjspp00bL0S0e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,
4613X-101-103LF,1,Bourns,4613X-101-103LF,https://octopart.com/4613x-101-103lf-bourns-1656444,Res Thick Film NET 10K Ohm 2% 1.63W ±100ppm/°C BUS Conformal 13-Pin SIP Pin Thru-Hole Bulk,,RA1,,,15w,Compliant,1,4613X-101-103LF-ND,652-4613X-1LF-10K,67AC8758,4613X-101-103LF,,Bulk,Bulk,,Bulk,,0.75,0.59,0.643,,,887,704,541,0,,1,1,1,500,,https://octopart.com/opatz8j6/a1?t=_sZYffgFWBRTeVaEua7Ignd49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,https://octopart.com/opatz8j6/a1?t=w9xrh7ZivARVW_qgDKW-koXHq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,https://octopart.com/opatz8j6/a1?t=hXIKxRHOu0OaJmGDVy5IRL_gw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,https://octopart.com/opatz8j6/a1?t=uB7S5sZ6ve7lTfH5vZi4Pg7lC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,,Mouser,652-4613X-1LF-10K,Bulk,0.59,0.59,0.59,704,1,https://octopart.com/opatz8j6/a1?t=w9xrh7ZivARVW_qgDKW-koXHq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,
RC0805FR-076K8L,4,Yageo,RC0805FR-076K8L,,6.8 kohm 1% 0805 thick-film resistor,Four discrete pull-ups replace RA2 common-bus array,"R20, R21, R22, R23",,,,,4,,,,,,,,,,,,,,,,,,,,,,,,,,,,,,,,,,,,,,,,
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
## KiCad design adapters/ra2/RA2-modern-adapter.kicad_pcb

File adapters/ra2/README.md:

# RA2 modern resistor adapter — revision A prototype

Open `RA2-modern-adapter.kicad_pro` in KiCad 10, then open the schematic or PCB.

This stand-alone adapter replaces the electrical function of OpenTendo RA2 with
four Yageo RC0805FR-076K8L resistors (6.8 kΩ, 1%, 0805). The two-layer board is
13 × 7 mm and specifies 0.8 mm thickness. Components are on the front; pin numbers
and the common-pin marking are on the back. Each resistor body is nominally
2.0 × 1.25 mm. The hand-solder footprint uses 1.20 × 1.40 mm pads with their
centers 2.0 mm apart.

## Pin mapping

| Motherboard RA2 pin / adapter J1 pin | Connection |
| --- | --- |
| 1 | VCC, common end of all four resistors |
| 2 | OUT-0 through R1 |
| 3 | PPU-A13 through R2 |
| 4 | /OE1 through R3 |
| 5 | /OE2 through R4 |

The five mounting holes are on 2.54 mm centers, spanning 10.16 mm. Pin 1 has a
square pad. It must connect to RA2's original common pin; reversing the assembly
changes the circuit. The intended mounting is upright with five short formed
round wire leads, nominally 0.5 mm diameter. Lead lengths, bend geometry and
clearance have not been qualified. Do not assume 0.64 mm square header pins fit
the motherboard's nominal 0.8 mm drilled holes.

## Evidence and checks

The upstream schematic was fetched from
<https://github.com/Redherring32/OpenTendo/blob/master/Board%20Files/Motherboard.kicad_sch>.
GitHub reported file blob `fe3801181a59c6be0fa255e838c7241576a137fa` when inspected.
The source is in `../../Board Files/Motherboard.kicad_sch`; the upstream license
is at `../../LICENSE`. Its exported netlist establishes the mapping above.
The schematic assigns `Resistor_THT:R_Array_SIP5`; the locally installed KiCad
library defines its five holes at 2.54 mm pitch with 0.8 mm drills.

KiCad 10.0.8 reports zero ERC violations, zero DRC violations, zero unconnected
items, and zero schematic parity issues for this prototype. Reports and a netlist
are in `checks/`. These checks do not verify physical fit, lead mechanics, or
function in a powered NES. The complete upstream motherboard PCB could not be
retrieved with the connected file tool because it exceeded its size limit;
neighboring component clearance has therefore not been checked. Match the target
board revision before ordering parts or PCBs. No Gerber manufacturing release
has been prepared.

The resistor selection uses the manufacturer specification at
<https://www.yageogroup.com/component-documentation/download/specsheet/RC0805FR-076K8L>.
Distributor stock was not checked for this prototype. Wire lead and PCB suppliers
remain unselected; see `BOM.csv`.

`build_adapter.py` regenerates the files with the installed KiCad bundled Python
and libraries. Regeneration replaces hand edits. On this Mac:

```sh
/Applications/KiCad/KiCad.app/Contents/Frameworks/Python.framework/Versions/3.9/bin/python3 build_adapter.py
```

The build script emits a KiCad wx initialization assertion in headless mode;
the saved files are independently parsed and checked by `kicad-cli`.

This project covers RA2 only. Diode, transistor, trimmer and connector replacement
designs have not been implemented or validated here.

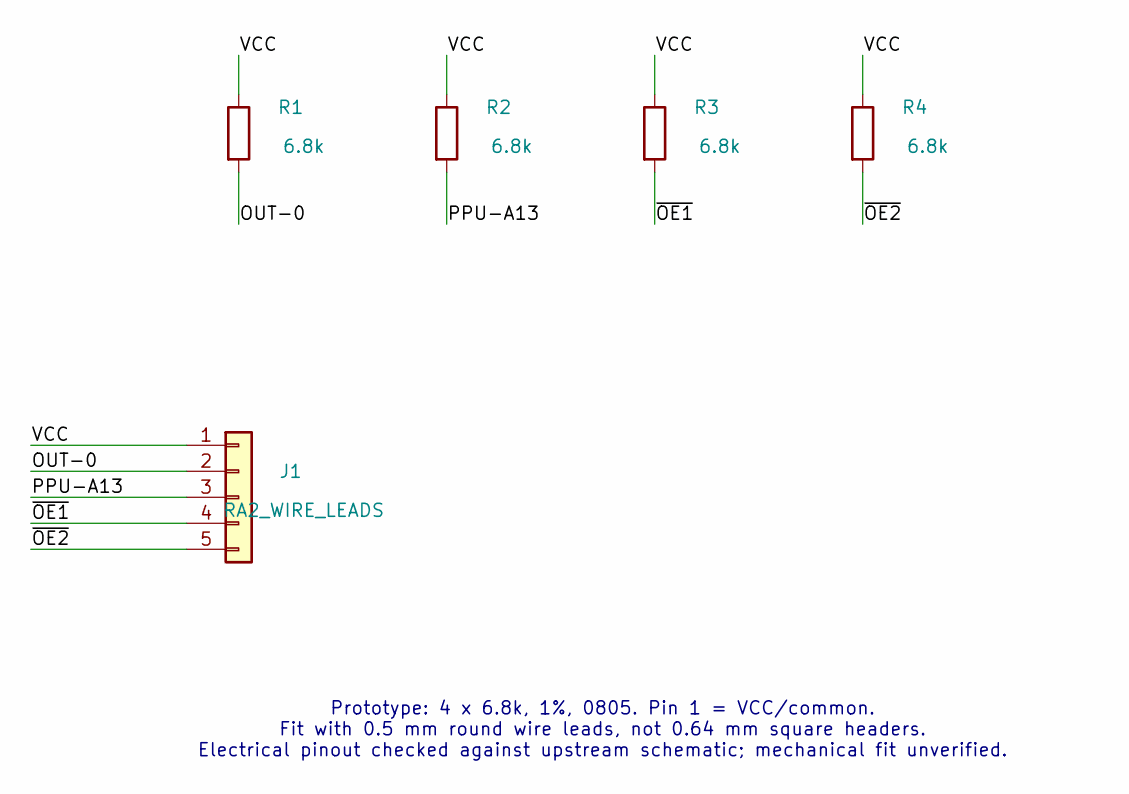
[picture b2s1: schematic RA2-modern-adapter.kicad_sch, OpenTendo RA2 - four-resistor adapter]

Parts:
J1: RA2_WIRE_LEADS; SIP5_WireLeads_P2.54mm
R1, R2, R3, R4: 6.8k; R_0805_2012Metric_Pad1.20x1.40mm_HandSolder; MPN RC0805FR-076K8L

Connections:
/OUT-0: J1.2, R1.2
/PPU-A13: J1.3, R2.2
/VCC: J1.1, R1.1, R2.1, R3.1, R4.1
/~OE1: J1.4, R3.2
/~OE2: J1.5, R4.2

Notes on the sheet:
Prototype: 4 x 6.8k, 1%, 0805. Pin 1 = VCC/common. Fit with 0.5 mm round wire leads, not 0.64 mm square headers. Electrical pinout checked against upstream schematic; mechanical fit unverified.

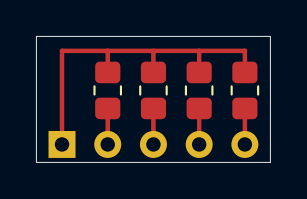
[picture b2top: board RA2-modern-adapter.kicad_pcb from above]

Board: 2 copper layers, 13.0 x 7.0 mm, 5 parts (0 on the bottom side), 5 nets.

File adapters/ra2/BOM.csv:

Reference,Quantity,Manufacturer,Part number,Description
"R1 R2 R3 R4",4,Yageo,RC0805FR-076K8L,"6.8 kohm 1% 0805 resistor"
J1,5,Unselected,Unselected,"0.5 mm diameter round tinned copper wire leads cut to length; qualify mechanically"
PCB,1,Unselected,RA2-modern-adapter,"13 x 7 mm 2-layer 0.8 mm prototype board"
